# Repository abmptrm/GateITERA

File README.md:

### Maket Gerbang ITERA
## MAX487 Communication

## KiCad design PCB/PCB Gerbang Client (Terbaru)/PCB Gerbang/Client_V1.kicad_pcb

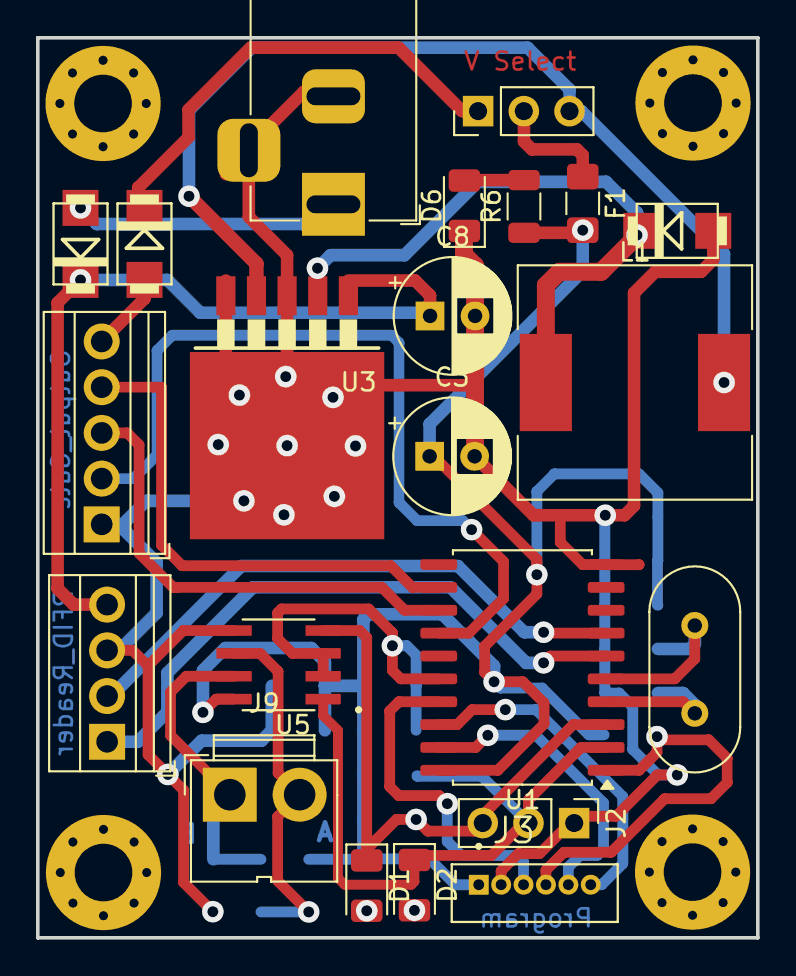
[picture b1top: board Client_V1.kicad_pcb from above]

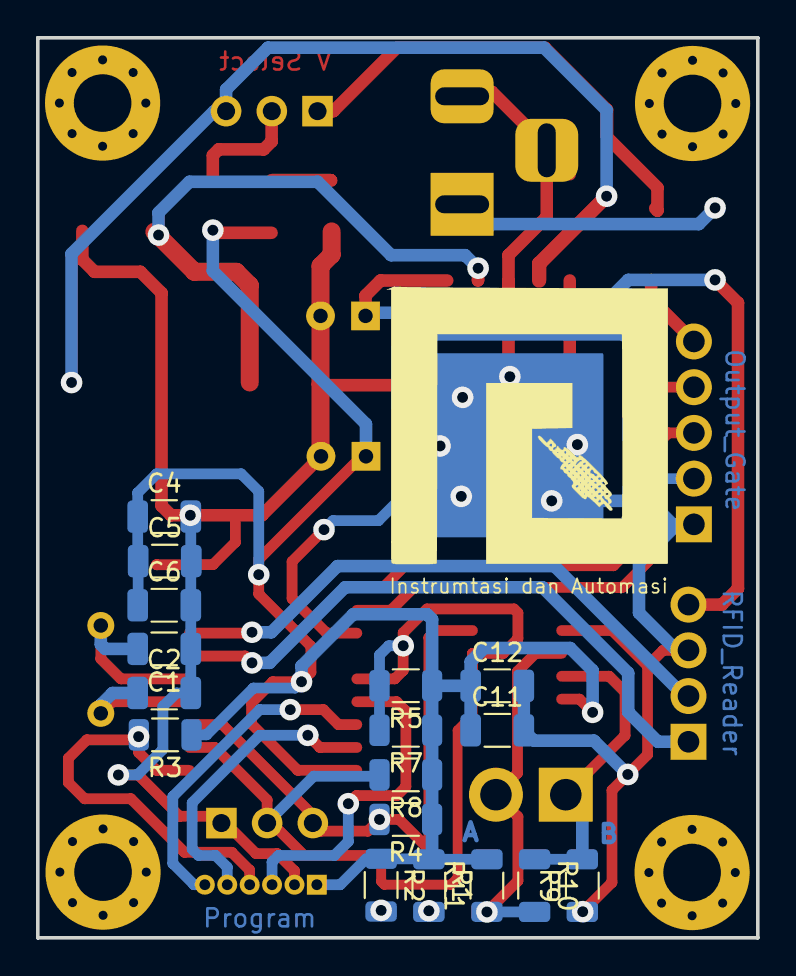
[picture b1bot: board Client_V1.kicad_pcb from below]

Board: 2 copper layers, 40.0 x 50.0 mm, 43 parts (17 on the bottom side), 28 nets.

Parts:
C1, C2: 22 pf; C_1206_3216Metric
C3, C8: 100uF; CP_Radial_D6.3mm_P2.50mm
C4: 1uF; C_1206_3216Metric
C5: 10uF; C_1206_3216Metric
C6: 100 nf; C_1206_3216Metric
C11: 10uf; C_1206_3216Metric
C12: 0.1uf; C_1206_3216Metric
D1: RX; LED_1206_3216Metric
D2: TX; LED_1206_3216Metric
D3, D5, D7: SS36; SMA
D6: POWER1; LED_1206_3216Metric
F1: Polyfuse_Small; Fuse_1206_3216Metric_Pad1.42x1.75mm_HandSolder
H1, H2, H3, H4: MountingHole_Pad; MountingHole_3.2mm_M3_Pad_Via
J1: V Select; PinHeader_1x03_P2.54mm_Vertical
J2: Debug_Pin; PinHeader_1x03_P2.54mm_Vertical
J3: Program; TE_1734598-6
J4: Output_Gate; TerminalBlock_Xinya_XY308-2.54-5P_1x05_P2.54mm_Horizontal
J5: RFID_Reader; TerminalBlock_Xinya_XY308-2.54-4P_1x04_P2.54mm_Horizontal
J6: DC-005-5A-2.0; BarrelJack_Horizontal
J9: RS485 IN/OUT; JWT_A3963_1x02_P3.96mm_Vertical
L1: 33uH; L_Sunlord_SWRB1204S
R1, R2, R3, R4, R5, R6, R7, R8: 10K; R_1206_3216Metric
R9, R11: 20K; R_1206_3216Metric
R10: 120; R_1206_3216Metric
U1: ATtiny4313-S; SOIC-20W_7.5x12.8mm_P1.27mm
U3: LM2596ADJ
U5: MAX485E; SOIC127P600X175-8N
Y1: 11.059 Mhz; Crystal_HC49-4H_Vertical

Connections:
5v_dari_Gerbang: D3.C, J1.1
+5V1: C3.1, C4.1, C5.1, C6.1, C11.1, C12.1, F1.2, J3.1, R1.1, R2.1, R3.1, R4.1, R5.1, R6.1, R7.1, R8.1, R11.2, U1.20 (VCC), U5.8 (VCC)
+12VDC: C8.1, D7.C, J5.4, U3.1 (VIN)
GND1: C1.1, C2.2, C3.2, C4.2, C5.2, C6.2, C8.2, C11.2, C12.2, D5.A, D6.1 (K), J2.1, J3.2, J4.1, J5.3, J6.2, J6.3, R9.1, U1.10 (GND), U3.3 (GND), U3.5 (~ON/OFF), U3.6 (GND), U5.5 (GND)
INT0: J5.1, U1.6 (PD2)
INT1: J5.2, U1.7 (PD3)
MISO: J3.6, U1.18 (PB6)
MOSI: J3.3, U1.17 (PB5)
unnamed: D1.2 (A), R1.2
unnamed: D2.2 (A), R2.2
unnamed: D3.A, J4.5
unnamed: D6.2 (A), R6.2
unnamed: D7.A, J6.1
unnamed: F1.1, J1.2
unnamed: J1.3, L1.2, U3.4 (FB)
unnamed: J9.1, R9.2, R10.1, U5.7 (B)
unnamed: J9.2, R10.2, R11.1, U5.6 (A)
unnamed: C1.2, U1.5 (PA0/XTAL1), Y1.1
unnamed: C2.1, U1.4 (PA1/XTAL2), Y1.2
unnamed: R5.2, R7.2, U1.16 (PB4), U5.2 (~RE), U5.3 (DE)
unnamed: D5.C, L1.1, U3.2 (OUT)
PIN 9: J4.4, U1.12 (PB0)
PIN 10: J4.3, U1.13 (PB1)
PIN 11: J4.2, U1.14 (PB2)
RESET: J3.4, R3.2, U1.1 (PA2/~RESET)
RX1: D2.1 (K), J2.2, R8.2, U1.2 (PD0), U5.1 (RO)
SCK: J3.5, U1.19 (PB7)
TX1: D1.1 (K), J2.3, R4.2, U1.3 (PD1), U5.4 (DI)
